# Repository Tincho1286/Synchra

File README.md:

# Synchra

**Plataforma experimental de control electrónico para motores brushless y radio control.**

Synchra reúne el desarrollo de un controlador electrónico de velocidad (ESC) sensorless basado en Arduino/ATmega328, su electrónica asociada y un sistema de control remoto. El objetivo principal es estudiar la conmutación trifásica y la detección de fuerza contraelectromotriz (BEMF) para ensayar el arranque y el funcionamiento de motores BLDC en lazo abierto y cerrado. Como parte de esta plataforma, también se explora la comunicación de radio y su futura evolución hacia LoRa en 433 MHz.

> Todo el firmware, los esquemáticos y las PCB se encuentran en desarrollo. Los archivos publicados registran etapas de diseño y ensayo; ninguno de los programas constituye una versión final lista para uso.

## Alcance del proyecto

El ESC constituye el núcleo de Synchra. Su firmware permite explorar la secuencia de conmutación del motor y la lectura de BEMF mediante el comparador analógico, mientras que los programas de ensayo abordan por separado el arranque, la sincronización y las pruebas de lazo cerrado.

Para controlar esta etapa se desarrolló un prototipo de transmisión y recepción con nRF24L01/RF24, con señales de aceleración y dirección. Ese trabajo sirve como punto de partida para la futura integración de un enlace LoRa de 433 MHz con un módulo EBYTE E32 y una nueva antena. La integración LoRa está prevista y todavía no forma parte del firmware publicado.

Ambas áreas se apoyan en los proyectos KiCad del ESC y del control remoto. Sus esquemáticos están disponibles para revisión, mientras que el diseño y el ruteo de las PCB continúan en proceso.

## Registro visual del proceso

Las siguientes imágenes muestran distintas etapas del desarrollo. Se agrupan por su contenido y orientación para relacionar los prototipos electrónicos, su montaje en la plataforma de prueba y las mediciones realizadas en banco. Cada fotografía enlaza con su archivo original para consultar los detalles.

### Prototipos y plataforma de prueba

Los prototipos del ESC y sus placas documentan las primeras etapas de construcción. Junto a ellos se presenta el vehículo de **DukeDoks** utilizado como plataforma mecánica para los ensayos del proyecto.

<table>
  <tr>
    <td width="33%" align="center" valign="top"></td>
    <td width="33%" align="center" valign="top"></td>
    <td width="34%" align="center" valign="top"></td>
  </tr>
  <tr>
    <td align="center"><sub>Prototipo previo del ESC.</sub></td>
    <td align="center"><sub>PCB correspondiente a una etapa previa.</sub></td>
    <td align="center"><sub>Plataforma mecánica de DukeDoks.</sub></td>
  </tr>
</table>

### Montajes experimentales

Estas etapas de construcción se complementan con los registros del montaje electrónico, el conjunto de transmisión y el control remoto de prototipo. Las fotografías permiten observar los elementos utilizados durante las pruebas, sin representar una configuración final del sistema.

<table>
  <tr>
    <td width="33%" align="center" valign="top"></td>
    <td width="33%" align="center" valign="top"></td>
    <td width="34%" align="center" valign="top"></td>
  </tr>
  <tr>
    <td align="center"><sub>Montaje previo del ESC.</sub></td>
    <td align="center"><sub>Conjunto de transmisión en ensayo.</sub></td>
    <td align="center"><sub>Control remoto de prototipo.</sub></td>
  </tr>
</table>

### Mediciones de banco

Además de documentar los montajes, el registro incluye mediciones de conmutación y señales de accionamiento. Estas capturas muestran las observaciones realizadas durante la experimentación y se complementan con una medición multicanal, presentada a mayor tamaño para facilitar la lectura de la pantalla.

<table>
  <tr>
    <td width="50%" align="center" valign="top"></td>
    <td width="50%" align="center" valign="top"></td>
  </tr>
  <tr>
    <td align="center"><sub>Medición de conmutación de fase.</sub></td>
    <td align="center"><sub>Señales de accionamiento del motor.</sub></td>
  </tr>
</table>

<p align="center">
  <br />
  <sub>Medición multicanal con instrumentación de laboratorio.</sub>
</p>

## Organización del repositorio

El código, las fuentes de hardware y los registros de ensayo se conservan en áreas separadas para facilitar su revisión. La documentación describe cómo se relacionan, mientras que las exportaciones históricas de fabricación permanecen identificadas en el archivo del proyecto.

| Directorio | Contenido |
| --- | --- |
| [`firmware/`](firmware/) | Firmware del ESC, prototipo de radio RF24 y programas de ensayo. |
| [`hardware/`](hardware/) | Proyectos KiCad del ESC y del control remoto. |
| [`archive/`](archive/) | Gerbers históricos de etapas anteriores. |
| [`media/`](media/) | Fotografías de prototipos, montajes y mediciones. |
| [`docs/`](docs/) | Arquitectura, estado de desarrollo y referencias. |

## Estado actual y continuidad

El núcleo del ESC y sus pruebas de sincronización forman la base activa del proyecto. A partir de este trabajo, las próximas líneas de desarrollo incluyen la integración LoRa de 433 MHz y la evolución de las PCB. El enlace RF24 se conserva como prototipo previo, y los Gerbers de `archive/historical-gerbers/` son registros históricos que no representan una revisión final de fabricación.

La [arquitectura](docs/architecture.md) explica la relación entre los componentes, y el [estado de desarrollo](docs/status.md) detalla la situación de cada área. Ambos documentos se complementan con las [referencias y atribuciones](docs/references.md), donde se identifica el alcance de los aportes externos.

## Créditos y referencias

El vehículo y los modelos empleados como plataforma de prueba pertenecen a **DukeDoks**. Sobre esa plataforma mecánica se ensaya la electrónica de Synchra, cuyo firmware y diseño electrónico fueron desarrollados específicamente para este proyecto.

Durante la investigación se consultaron los proyectos de **Electronoobs** y otros ESC públicos como referencias de aprendizaje. Para la futura integración LoRa también se utiliza la documentación técnica de EBYTE E32. El alcance de estas referencias se describe en [`docs/references.md`](docs/references.md).

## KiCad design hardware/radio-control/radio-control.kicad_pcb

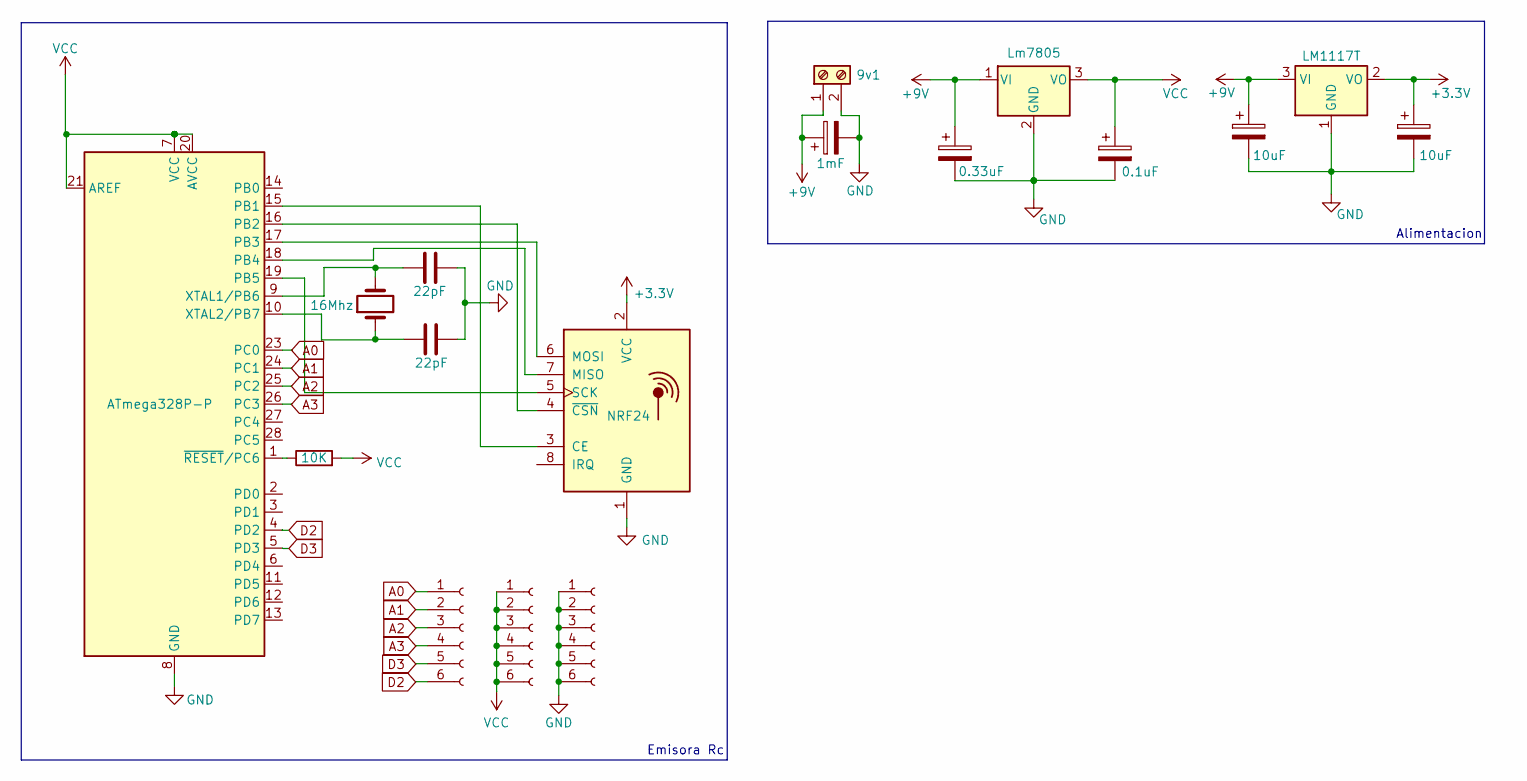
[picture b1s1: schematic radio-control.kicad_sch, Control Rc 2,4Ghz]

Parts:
9v1: Screw_Terminal_01x02; TerminalBlock_bornier-2_P5.08mm
C1, C2: 22pF; C_Disc_D5.0mm_W2.5mm_P2.50mm
C3: 1mF; CP_Radial_D10.0mm_P5.00mm
C4: 0.33uF; CP_Radial_D4.0mm_P1.50mm
C5: 0.1uF; CP_Radial_D4.0mm_P1.50mm
C6, C7: 10uF; CP_Radial_D4.0mm_P1.50mm
J1, J2, J3: Conn_01x06_Socket; PinHeader_1x06_P2.54mm_Vertical
K1: 16Mhz; Crystal_HC49-U_Vertical
R1: 10K; R_Axial_DIN0411_L9.9mm_D3.6mm_P15.24mm_Horizontal
U1: ATmega328P-P; DIP-28_W7.62mm
U2: NRF24; nRF24L01_Breakout
U3: Lm7805; TO-220-3_Vertical
U4: LM1117T; TO-220-3_Vertical

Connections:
+3.3V: C7.1, U2.2 (VCC), U4.2 (VO)
+9V: 9v1.1, C3.1, C4.1, C6.1, U3.1 (VI), U4.3 (VI)
A0: J1.1, U1.23 (PC0)
A1: J1.2, U1.24 (PC1)
A2: J1.3, U1.25 (PC2)
A3: J1.4, U1.26 (PC3)
D2: J1.6, U1.4 (PD2)
D3: J1.5, U1.5 (PD3)
GND: 9v1.2, C1.2, C2.2, C3.2, C4.2, C5.2, C6.2, C7.2, J3.1, J3.2, J3.3, J3.4, J3.5, J3.6, U1.8 (GND), U1.22 (GND), U2.1 (GND), U3.2 (GND), U4.1 (GND)
unnamed: U1.15 (PB1), U2.3 (CE)
unnamed: U1.16 (PB2), U2.4 (~CSN)
unnamed: U1.17 (PB3), U2.6 (MOSI)
unnamed: U1.18 (PB4), U2.7 (MISO)
unnamed: U1.19 (PB5), U2.5 (SCK)
unnamed: C1.1, K1.2, U1.9 (XTAL1/PB6)
unnamed: C2.1, K1.1, U1.10 (XTAL2/PB7)
unnamed: R1.1, U1.1 (~RESET/PC6)
VCC: C5.1, J2.1, J2.2, J2.3, J2.4, J2.5, J2.6, R1.2, U1.7 (VCC), U1.20 (AVCC), U1.21 (AREF), U3.3 (VO)

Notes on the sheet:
Alimentacion
Emisora Rc

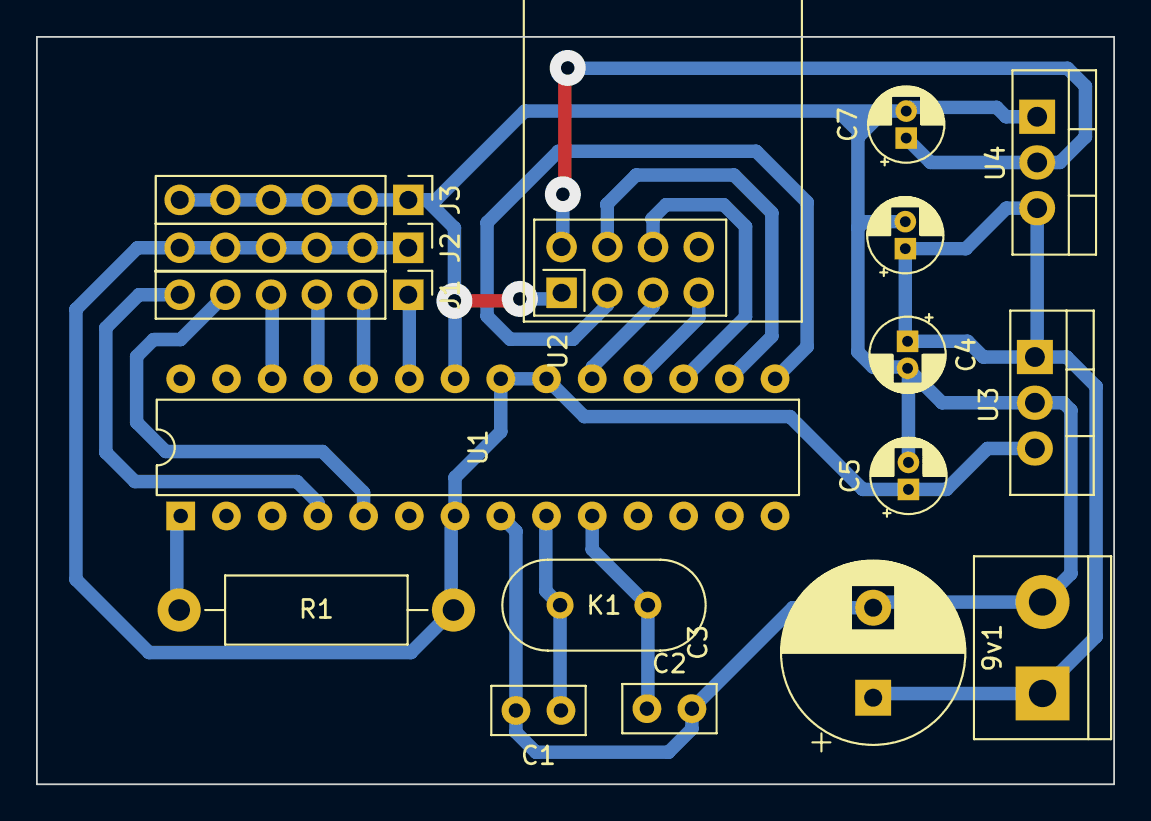
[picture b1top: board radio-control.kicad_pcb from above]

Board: 2 copper layers, 59.8 x 41.5 mm, 17 parts (0 on the bottom side), 18 nets.

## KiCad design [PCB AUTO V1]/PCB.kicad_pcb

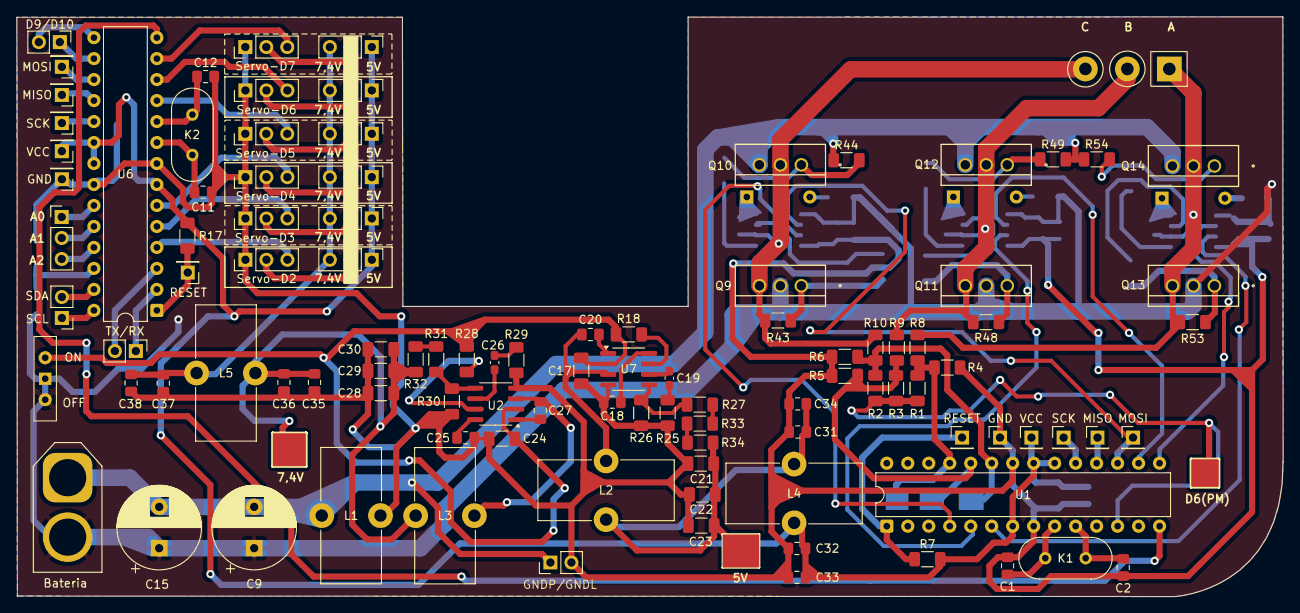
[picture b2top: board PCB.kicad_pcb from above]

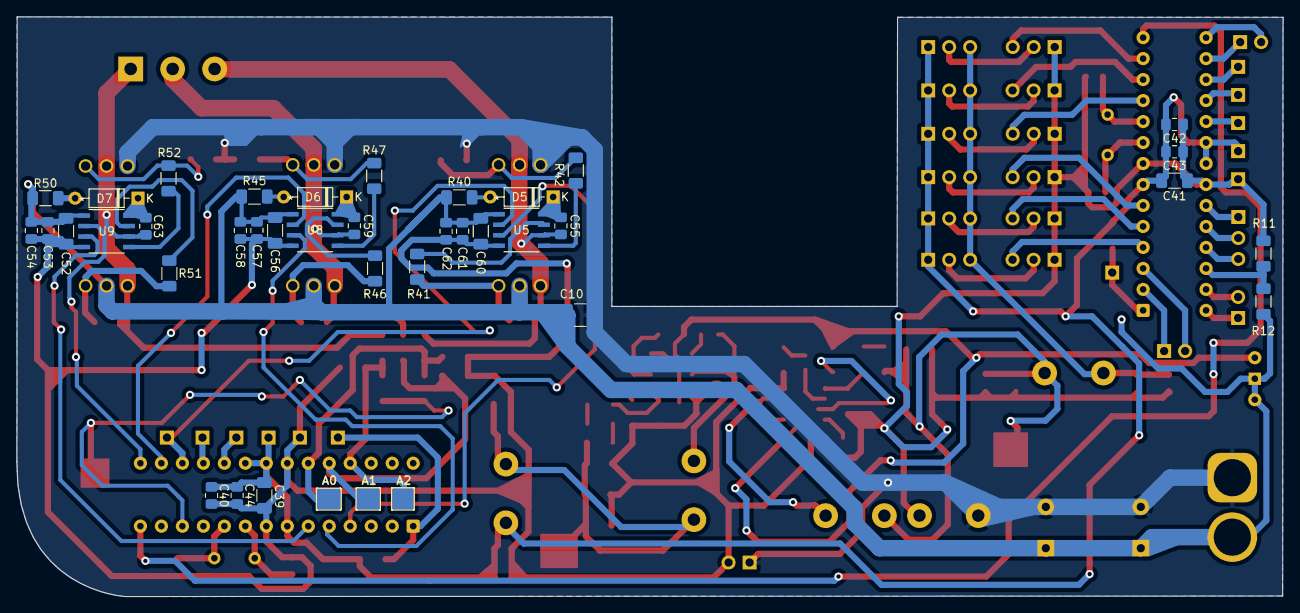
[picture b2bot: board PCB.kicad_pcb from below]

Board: 2 copper layers, 153.3 x 70.2 mm, 141 parts (36 on the bottom side), 90 nets.

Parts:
C1, C2, C11, C12: 22pF; C_0805_2012Metric_Pad1.18x1.45mm_HandSolder
C9, C15: 1mF; CP_Radial_D10.0mm_P5.00mm
C10: 22uF; C_1210_3225Metric_Pad1.33x2.70mm_HandSolder
C17, C21, C22, C23, C24, C28, C29, C30, C39, C41, C52, C56, C60: 22uF; C_1206_3216Metric_Pad1.33x1.80mm_HandSolder
C18, C25, C33, C34, C35, C38, C40, C42, C54, C58, C62: 0.1uF; C_0805_2012Metric_Pad1.18x1.45mm_HandSolder
C19, C26: 3.9nF; C_0603_1608Metric_Pad1.08x0.95mm_HandSolder
C20, C27: 10nF; C_0805_2012Metric_Pad1.18x1.45mm_HandSolder
C31, C32, C36, C37, C43, C44, C53, C55, C57, C59, C61, C63: 10uF; C_0805_2012Metric_Pad1.18x1.45mm_HandSolder
Con1: Bateria; AMASS_XT60-M_1x02_P7.20mm_Vertical
Con2: ABC; TerminalBlock_bornier-3_P5.08mm
Conn1: GNDP/GNDL; PinHeader_1x02_P2.54mm_Vertical
Conn2: A6; PinHeader_1x03_P2.54mm_Vertical
Conn3: A1; PinHeader_1x03_P2.54mm_Vertical
Conn4: A2; PinHeader_1x03_P2.54mm_Vertical
Conn5: A3; PinHeader_1x03_P2.54mm_Vertical
Conn6: A4; PinHeader_1x03_P2.54mm_Vertical
Conn7: A5; PinHeader_1x03_P2.54mm_Vertical
Conn8: TX/RX; PinHeader_1x02_P2.54mm_Vertical
Conn9: D9/D10; PinHeader_1x02_P2.54mm_Vertical
Conn10: Entradas analogicas; PinHeader_1x03_P2.54mm_Vertical
Conn11: SDA/SCL; PinHeader_1x02_P2.54mm_Vertical
Conn12: Servo-D2; PinHeader_1x03_P2.54mm_Vertical
Conn13: Servo-D3; PinHeader_1x03_P2.54mm_Vertical
Conn14: Servo-D4; PinHeader_1x03_P2.54mm_Vertical
Conn15: Servo-D5; PinHeader_1x03_P2.54mm_Vertical
Conn16: Servo-D6; PinHeader_1x03_P2.54mm_Vertical
Conn17: Servo-D7; PinHeader_1x03_P2.54mm_Vertical
D5, D6, D7: 1N4148; D_DO-35_SOD27_P7.62mm_Horizontal
GND: Conn_01x01_Socket; PinHeader_1x01_P2.54mm_Vertical
GND#2: Conn_01x01_Socket; PinHeader_1x01_P2.54mm_Vertical
K1, K2: 16Mhz; Crystal_HC49-U_Vertical
L1, L4, L5: 100uH; L_Toroid_Vertical_L16.3mm_W7.1mm_P7.11mm_Pulse_H
L2, L3: 10uH; L_Toroid_Vertical_L16.3mm_W7.1mm_P7.11mm_Pulse_H
MISO: Conn_01x01_Socket; PinHeader_1x01_P2.54mm_Vertical
MISO#2: Conn_01x01_Socket; PinHeader_1x01_P2.54mm_Vertical
MOSI: Conn_01x01_Socket; PinHeader_1x01_P2.54mm_Vertical
MOSI#2: Conn_01x01_Socket; PinHeader_1x01_P2.54mm_Vertical
Q9, Q10, Q11, Q12, Q13, Q14: CSD18510KCS; KCS3
R1, R2, R3, R8, R9, R10, R27: 33K; R_1206_3216Metric_Pad1.30x1.75mm_HandSolder
R4, R5, R6, R7, R11, R17, R26, R30, R33, R43, R44, R48, R49, R53, R54: 10K; R_1206_3216Metric_Pad1.30x1.75mm_HandSolder
R12: 20K; R_1206_3216Metric_Pad1.30x1.75mm_HandSolder
R18, R28: 100K; R_1206_3216Metric_Pad1.30x1.75mm_HandSolder
R25, R29: 6.8K; R_1206_3216Metric_Pad1.30x1.75mm_HandSolder
R31: 66K; R_1206_3216Metric_Pad1.30x1.75mm_HandSolder
R32: 3.9K; R_1206_3216Metric_Pad1.30x1.75mm_HandSolder
R34: 1K2; R_1206_3216Metric_Pad1.30x1.75mm_HandSolder
R40, R45, R50: ?; R_1206_3216Metric_Pad1.30x1.75mm_HandSolder
R41, R42, R46, R47, R51, R52: 10; R_1206_3216Metric_Pad1.30x1.75mm_HandSolder
RESET: Conn_01x01_Socket; PinHeader_1x01_P2.54mm_Vertical
RESET#2: Conn_01x01_Socket; PinHeader_1x01_P2.54mm_Vertical
SCK: Conn_01x01_Socket; PinHeader_1x01_P2.54mm_Vertical
SCK#2: Conn_01x01_Socket; PinHeader_1x01_P2.54mm_Vertical
SW1: SW; SW_Slide-03_Wuerth-WS-SLTV_10x2.5x6.4_P2.54mm
U1, U6: ATmega328P-P; DIP-28_W7.62mm
U2, U7: MP2307; SOIC-8_3.9x4.9mm_P1.27mm
U5, U8, U9: LM2104DR; SOIC8_D_TEX
VCC: Conn_01x01_Socket; PinHeader_1x01_P2.54mm_Vertical
VCC#2: Conn_01x01_Socket; PinHeader_1x01_P2.54mm_Vertical

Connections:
5v-M1: C32.2, C33.2, C39.2, C40.2, C41.2, C42.2, C43.2, C44.2, Conn2.1, Conn3.1, Conn4.1, Conn5.1, Conn6.1, Conn7.1, L4.2, R7.2, R17.2, U1.7 (VCC), U1.20 (AVCC), U1.21 (AREF), U6.7 (VCC), U6.20 (AVCC), U6.21 (AREF), VCC.1, VCC#2.1
7,4v-Filtrado: C37.2, C38.2, Conn2.3, Conn3.3, Conn4.3, Conn5.3, Conn6.3, Conn7.3, L5.2
+12V: C9.1, C10.1, C15.1, C52.2, C53.2, C54.1, C56.2, C57.2, C58.1, C60.2, C61.2, C62.1, Con1.2, Q9.2 (D), Q11.2 (D), Q13.2 (D), R12.2, R40.2, R45.2, R50.2, SW1.1, SW1.3, U5.1 (GVDD), U8.1 (GVDD), U9.1 (GVDD)
+BATT: C17.1, C24.1, R18.2, R28.2, SW1.2, U2.2 (IN), U7.2 (IN)
A: C63.2, Con2.1, Q13.3 (S), Q14.2 (D), R8.2, R53.1, U9.6 (SH)
A0: R2.2, R6.2, R10.1, U1.23 (PC0)
A0-M2: Conn10.1, U6.23 (PC0)
A1: R3.2, R5.1, R9.1, U1.24 (PC1)
A1-M2: Conn10.2, U6.24 (PC1)
A2: R1.2, R4.2, R8.1, U1.25 (PC2)
A2-M2: Conn10.3, U6.25 (PC2)
A3-M2: R11.2, R12.1, U6.26 (PC3)
AH: U1.15 (PB1), U9.2 (IN)
AL: U1.6 (PD4), U9.3 (*SD)
AL1: Conn3.2, Conn12.2
AL2: Conn4.2, Conn13.2
AL3: Conn5.2, Conn14.2
AL4: Conn6.2, Conn15.2
AL5: Conn7.2, Conn16.2
AL6: Conn2.2, Conn17.2
B: C59.2, Con2.2, Q11.3 (S), Q12.2 (D), R9.2, R48.1, U8.6 (SH)
BH: U1.16 (PB2), U8.2 (IN)
BL: U1.5 (PD3), U8.3 (*SD)
C: C55.2, Con2.3, Q9.3 (S), Q10.2 (D), R10.2, R43.1, U5.6 (SH)
CH: MOSI#2.1, U1.17 (PB3), U5.2 (IN)
CL: U1.4 (PD2), U5.3 (*SD)
D2-M2: Conn12.3, U6.4 (PD2)
D3-M2: Conn13.3, U6.5 (PD3)
D4-M2: Conn14.3, U6.6 (PD4)
D5-M2: Conn15.3, U6.11 (PD5)
D6: R1.1, R2.1, R3.1, U1.12 (PD6)
D6-M2: Conn16.3, U6.12 (PD6)
D7-M2: Conn17.3, U6.13 (PD7)
D9-M2: Conn9.2, U6.15 (PB1)
D10-M2: Conn9.1, U6.16 (PB2)
GND-M1: C1.2, C2.2, C11.2, C12.2, C17.2, C18.2, C21.2, C22.2, C23.2, C24.2, C25.2, C28.2, C29.2, C30.2, C31.1, C32.1, C33.1, C34.1, C35.1, C36.1, C37.1, C38.1, C39.1, C40.1, C41.1, C42.1, C43.1, C44.1, C52.1, C53.1, C54.2, C56.1, C57.1, C58.2, C60.1, C61.1, C62.2, Conn1.2, Conn12.1, Conn13.1, Conn14.1, Conn15.1, Conn16.1, Conn17.1, GND.1, GND#2.1, L1.2, R4.1, R5.2, R6.1, R11.1, R25.2, R26.1, R29.2, R30.1, U1.8 (GND), U1.22 (GND), U2.4 (GND), U5.4 (GND), U6.8 (GND), U6.22 (GND), U7.4 (GND), U8.4 (GND), U9.4 (GND)
GNDB: C9.2, C10.2, C15.2, Con1.1, Conn1.1, L1.1, Q10.3 (S), Q12.3 (S), Q14.3 (S), R44.1, R49.1, R54.1
MISO-M1: MISO#2.1, U1.18 (PB4)
MISO-M2: MISO.1, U6.18 (PB4)
MOSI-M2: MOSI.1, U6.17 (PB3)
unnamed: C19.2, R25.1
unnamed: C26.2, R29.1
unnamed: D5.2 (A), R40.1
unnamed: C55.1, D5.1 (K), U5.8 (BST)
unnamed: D6.2 (A), R45.1
unnamed: C59.1, D6.1 (K), U8.8 (BST)
unnamed: D7.2 (A), R50.1
unnamed: C63.1, D7.1 (K), U9.8 (BST)
unnamed: Q9.1 (G), R41.2, R43.2
unnamed: Q10.1 (G), R42.2, R44.2
unnamed: Q11.1 (G), R46.2, R48.2
unnamed: Q12.1 (G), R47.2, R49.2
unnamed: Q13.1 (G), R51.2, R53.2
unnamed: Q14.1 (G), R52.2, R54.2
unnamed: R27.2, R33.1
unnamed: R31.2, R32.1
unnamed: R33.2, R34.1
unnamed: C27.1, U2.1 (BS)
unnamed: C26.1, U2.6 (COMP)
unnamed: R28.1, U2.7 (EN)
unnamed: R30.2, R31.1, U2.5 (FB)
unnamed: C25.1, U2.8 (SS)
unnamed: C27.2, L3.1, U2.3 (SW)
unnamed: R41.1, U5.7 (GH)
unnamed: R42.1, U5.5 (GL)
unnamed: C20.1, U7.1 (BS)
unnamed: C19.1, U7.6 (COMP)
unnamed: R18.1, U7.7 (EN)
unnamed: R26.2, R27.1, U7.5 (FB)
unnamed: C18.1, U7.8 (SS)
unnamed: C20.2, L2.1, U7.3 (SW)
unnamed: R46.1, U8.7 (GH)
unnamed: R47.1, U8.5 (GL)
unnamed: R51.1, U9.7 (GH)
unnamed: R52.1, U9.5 (GL)
PWM Motor: U1.14 (PB0), U6.14 (PB0)
RESET-M1: R7.1, RESET#2.1, U1.1 (~RESET/PC6)
RESET-M2: R17.1, RESET.1, U6.1 (~RESET/PC6)
RX: Conn8.1, U6.2 (PD0)
SCK-M1: SCK.1, U1.19 (PB5)
SCK-M2: SCK#2.1, U6.19 (PB5)
SCL: Conn11.1, U6.28 (PC5)
SDA: Conn11.2, U6.27 (PC4)
TX: Conn8.2, U6.3 (PD1)
VCC: C21.1, C22.1, C23.1, C31.2, C34.2, L2.2, L4.1, R34.2
VDD: C28.1, C29.1, C30.1, C35.2, C36.2, L3.2, L5.1, R32.2
XTAL1-M1: C1.1, K1.2, U1.9 (XTAL1/PB6)
XTAL1-M2: C11.1, K2.2, U6.9 (XTAL1/PB6)
XTAL2-M1: C2.1, K1.1, U1.10 (XTAL2/PB7)
XTAL2-M2: C12.1, K2.1, U6.10 (XTAL2/PB7)
